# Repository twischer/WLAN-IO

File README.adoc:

WLAN-IO
=======

WLAN-RGB-Para
-------------
The ESP8266 is used as an Art-Net-Node and the 3 output pins will be used as PWM outputs. So a RGB-LED could be directly connected and controlled over WLAN.
The inital version was copied from http://www.ulrichradig.de/home/index.php/dmx/wlan-art-net-node.

### Building WLAN-RGB-Para with MQTT and Art-Net support
    $ make COMPONENTS="io/mqtt io/pwm io/artnet"
See schematics/LEDDriver.sch

### Energy consumtion
Supply	Off				On
4,8V	75mA (360mW)
8V		75mA (600mW)	3,40A (27,2W)
10V						2,58A
12V						2,03A
14V						1,68A
15V		75mA (1,13W)	1,57A (23,6W)

Building for heater controll and DHT22 support controlling over MQTT
--------------------------------------------------------------------
    $ make COMPONENTS="io/mqtt io/heater io/dhtxx"
See schematics/dhtxx+heater.sch for a wiring example.

Building for shift phase dimmer with zero crossing detection
------------------------------------------------------------
This build supports MQTT, too.
It will be build for ESP8266 on the module ESP03.
Default is ESP02.
    $ make COMPONENTS="io/mqtt io/pwm io/pwm/zcd" DEFINES="-DESP03 -DPWM_CHANNEL=1 -DPWM_INVERTED"
See schematics/dimmerWall.sch for the needed components to run.

HOWTO test mosquitto (MQTT broker)
----------------------------------
    $ sudo apt-get install mosquitto mosquitto-clients

    $ mosquitto_pub -h [HOST] -m hello -t test -r

    $ mosquitto_sub -h [HOST] -t test -d

ESP-LINK: Wifi-Serial Bridge w/REST&MQTT
========================================
Thorsten von Eicken
:toc:
:toc-title!:
:toc-placement!:

This firmware connects an attached micro-controller to the internet using a ESP8266 Wifi module.
It implements a number of features:

[options="compact"]
- transparent bridge between Wifi and serial, useful for debugging or inputting into a uC
- flash-programming attached Arduino/AVR microcontrollers, esp8266 modules, as well as
  LPC800-series and other ARM microcontrollers via Wifi
- built-in stk500v1 programmer for AVR uC's: program using HTTP upload of hex file
- outbound REST HTTP requests from the attached micro-controller to the internet
- MQTT client pub/sub from the attached micro-controller to the internet

The firmware includes a tiny HTTP server based on
http://www.esp8266.com/viewforum.php?f=34[esphttpd]
with a simple web interface, many thanks to Jeroen Domburg for making it available!
The REST and MQTT functionality are loosely based on https://github.com/tuanpmt/espduino
but significantly reqritten and no longer protocol compatible, thanks to tuanpmt for the
inspiration!

Many thanks to https://github.com/brunnels for contributions in particular around the espduino
functionality. Thank you also to https://github.com/susisstrolch, https://github.com/bc547,
and https://github.com/katast for additional contributions!

[float]
Table of Contents
-----------------

toc::[]

Releases & Downloads
--------------------

- https://github.com/jeelabs/esp-link/releases/tag/v2.1.7[V2.1.7] is the most recent release.
  It has the new built-in stk500v1 programmer and works on all modules (esp-01 through esp-12).
- https://github.com/jeelabs/esp-link/releases/tag/v2.2.beta2[V2.2.beta2] will be coming
  up shortly with mDNS, sNTP, and syslog support, stay tuned...
- See https://github.com/jeelabs/esp-link/releases[all releases].

For quick support and questions chat at
image:https://badges.gitter.im/Join%20Chat.svg[link="https://gitter.im/jeelabs/esp-link"]

Intro
-----

### Esp-link goals

The goal of the esp-link project is to create an advanced Wifi co-processor. Esp-link assumes that
there is a "main processor" (also referred to as "attached uController") and that esp-link's role
is to facilitate communication over Wifi. Where esp-link is a bit unusual is that it's not really
just a Wifi interface or a slave co-processor. In some sense it's the master, because the main
processor can be reset, controlled and reprogrammed through esp-link. The three main areas of
functionality in esp-link are:

- reprogramming and debugging the attached uC
- letting the attached uC make outbound communication and offloading the protocol processing
- forwarding inbound communication and offloading the protocol processing (this part is the
least developed)

The goal of the project is also to remain focused on the above mission. In particular, esp-link
is not a platform for stand-alone applications and it does not support connecting sensors or
actuators directly to it. A few users have taken esp-link as a starting point for doing these
things and that's great, but there's also value in keeping the mainline esp-link project
focused on a clear mission.

### Esp-link uses

The simplest use of esp-link is as a transparent serial to wifi bridge. You can flash an attached
uC over wifi and you can watch the uC's serial debug output by connecting to port 23 or looking
at the uC Console web page.

The next level is to use the outbound connectivity of esp-link in the uC code. For example, the
uC can use REST requests to services like thingspeak.com to send sensor values that then get
stored and plotted by the external service.
The uC can also use REST requests to retrieve simple configuration
information or push other forms of notifications. (MQTT functionality is forthcoming.)

An additional option is to add code to esp-link to customize it and put all the communication
code into esp-link and only keep simple sensor/actuator control in the attached uC. In this
mode the attached uC sends custom commands to esp-link with sensor/acturator info and
registers a set of callbacks with esp-link that control sensors/actuators. This way, custom
commands in esp-link can receive MQTT messages, make simple callbacks into the uC to get sensor
values or change actuators, and then respond back with MQTT. The way this is architected is that
the attached uC registers callbacks at start-up such that the code in the esp doesn't need to 
know which exact sensors/actuators the attached uC has, it learns that through the initial
callback registration.

### Eye Candy

These screen shots show the Home page, the Wifi configuration page, the console for the
attached microcontroller, and the pin assignments card:

image:https://cloud.githubusercontent.com/assets/39480/8261425/6ca395a6-167f-11e5-8e92-77150371135a.png[width="45%"]
image:https://cloud.githubusercontent.com/assets/39480/8261427/6caf7326-167f-11e5-8085-bc8b20159b2b.png[width="45%"]
image:https://cloud.githubusercontent.com/assets/39480/8261426/6ca7f75e-167f-11e5-827d-9a1c582ad05d.png[width="45%"]
image:https://cloud.githubusercontent.com/assets/39480/8261658/11e6c64a-1681-11e5-82d0-ea5ec90a6ddb.png[width="45%"]

Getting Started
---------------

### Hardware configuration

This firmware is designed for any esp8266 module.
The recommended connections for an esp-01 module are:

- URXD: connect to TX of microcontroller
- UTXD: connect to RX of microcontroller
- GPIO0: connect to RESET of microcontroller
- GPIO2: optionally connect green LED to 3.3V (indicates wifi status)

The recommended connections for an esp-12 module are:

- URXD: connect to TX of microcontroller
- UTXD: connect to RX of microcontroller
- GPIO12: connect to RESET of microcontroller
- GPIO13: connect to ISP of LPC/ARM microcontroller or to GPIO0 of esp8266 being programmed
  (not used with Arduino/AVR)
- GPIO0: optionally connect green "conn" LED to 3.3V (indicates wifi status)
- GPIO2: optionally connect yellow "ser" LED to 3.3V (indicates serial activity)

If your application has problems with the boot message that is output at ~74600 baud by the ROM
at boot time you can connect an esp-12 module as follows and choose the "swap_uart" pin assignment
in the esp-link web interface:

- GPIO13: connect to TX of microcontroller
- GPIO15: connect to RX of microcontroller
- GPIO1/UTXD: connect to RESET of microcontroller
- GPIO3/URXD: connect to ISP of LPC/ARM microcontroller or to GPIO0 of esp8266 being programmed
  (not used with Arduino/AVR)
- GPIO0: optionally connect green "conn" LED to 3.3V (indicates wifi status)
- GPIO2: optionally connect yellow "ser" LED to 3.3V (indicates serial activity)

If you are using an FTDI connector, GPIO12 goes to DTR and GPIO13 goes to CTS (or vice-versa, I've
seen both used, sigh).

The GPIO pin assignments can be changed dynamically in the web UI and are saved in flash.

### Initial flashing

If you want to simply flash a pre-built firmware binary, you can download the latest
https://github.com/jeelabs/esp-link/releases[release] and use your favorite
ESP8266 flashing tool to flash the bootloader, the firmware, and blank settings.
Detailed instructions are provided in the release notes.

_Important_: the firmware adapts automatically to the size of the flash chip using information
stored in the boot sector (address 0). This is the standard way that the esp8266 SDK detects
the flash size. What this means is that you need to set this properly when you flash the bootloader.
If you use esptool.py you can do it using the -ff and -fs options.

### Wifi configuration overview

For proper operation the end state that esp-link needs to arrive at is to have it
join your pre-existing wifi network as a pure station.
However, in order to get there esp-link will start out as an access point and you'll have
to join its network to configure it. The short version is:

 1. esp-link creates a wifi access point with an SSID of the form `ESP_012ABC` (some modules
    use a different SSID form, such as `ai-thinker-012ABC`)
 2. you join your laptop or phone to esp-link's network as a station and you configure
    esp-link wifi with your network info by pointing your browser at `http://192.168.4.1/`
 3. you set a hostname for esp-link on the "home" page, or leave the default ("esp-link")
 4. esp-link starts to connect to your network while continuing to also be an access point
    ("AP+STA"), the esp-link may show up with a `${hostname}.local` hostname
    (depends on your DHCP/DNS config)
 4. esp-link succeeds in connecting and shuts down its own access point after 15 seconds,
    you reconnect your laptop/phone to your normal network and access esp-link via its hostname
    or IP address

### LED indicators

Assuming appropriate hardware attached to GPIO pins, the green "conn" LED will show the wifi
status as follows:

- Very short flash once a second: not connected to a network and running as AP+STA, i.e.
  trying to connect to the configured network
- Very short flash once every two seconds: not connected to a network and running as AP-only
- Even on/off at 1HZ: connected to the configured network but no IP address (waiting on DHCP)
- Steady on with very short off every 3 seconds: connected to the configured network with an
  IP address (esp-link shuts down its AP after 60 seconds)

The yellow "ser" LED will blink briefly every time serial data is sent or received by the esp-link.

### Troubleshooting

- verify that you have sufficient power, borderline power can cause the esp module to seemingly
  function until it tries to transmit and the power rail collapses
- if you just cannot flash your esp8266 module (some people call it the zombie mode) make sure you
  have gpio0 and gpio15 pulled to gnd with a 1K resistor, gpio2 tied to 3.3V with 1K resistor, and
  RX/TX connected without anything in series. If you need to level shift the signal going into the
  esp8266's RX use a 1K resistor. Use 115200 baud in the flasher.
  (For a permanent set-up I would use higher resistor values but
  when nothing seems to work these are the ones I try.)
- if the flashing succeeded, check the "conn" LED to see which mode esp-link is in (see LED info above)
- reset or power-cycle the esp-link to force it to become an access-point if it can't
  connect to your network within 15-20 seconds
- if the LED says that esp-link is on your network but you can't get to it, make sure your
  laptop is on the same network (and no longer on the esp's network)
- if you do not know the esp-link's IP address on your network, try `esp-link.local`, try to find
  the lease in your DHCP server; if all fails, you may have to turn off your access point (or walk
  far enough away) and reset/power-cycle esp-link, it will then fail to connect and start its
  own AP after 15-20 seconds

Configuration details
---------------------

### Wifi

After you have serially flashed the module it will create a wifi access point (AP) with an
SSID of the form `ESP_012ABC` where 012ABC is a piece of the module's MAC address.
Using a laptop, phone, or tablet connect to this SSID and then open a browser pointed at
http://192.168.4.1/, you should then see the esp-link web site.

Now configure the wifi. The desired configuration is for the esp-link to be a
station on your local wifi network so you can communicate with it from all your computers.

To make this happen, navigate to the wifi page and you should see the esp-link scan
for available networks. You should then see a list of detected networks on the web page and you
can select yours.
Enter a password if your network is secure (highly recommended...) and hit the connect button.

You should now see that the esp-link has connected to your network and it should show you
its IP address. _Write it down_. You will then have to switch your laptop, phone, or tablet
back to your network and then you can connect to the esp-link's IP address or, depending on your
network's DHCP/DNS config you may be able to go to http://esp-link.local

At this point the esp-link will have switched to STA mode and be just a station on your
wifi network. These settings are stored in flash and thereby remembered through resets and
power cycles. They are also remembered when you flash new firmware. Only flashing `blank.bin`
via the serial port as indicated above will reset the wifi settings.

There is a fail-safe, which is that after a reset or a configuration change, if the esp-link
cannot connect to your network it will revert back to AP+STA mode after 15 seconds and thus
both present its `ESP_012ABC`-style network and continue trying to reconnect to the requested network.
You can then connect to the esp-link's AP and reconfigure the station part.

One open issue (#28) is that esp-link cannot always display the IP address it is getting to the browser
used to configure the ssid/password info. The problem is that the initial STA+AP mode may use
channel 1 and you configure it to connect to an AP on channel 6. This requires the ESP8266's AP
to also switch to channel 6 disconnecting you in the meantime. 

### Hostname, description, DHCP, mDNS

You can set a hostname on the "home" page, this should be just the hostname and not a domain
name, i.e., something like "test-module-1" and not "test-module-1.mydomain.com".
This has a number of effects:

- you will see the first 12 chars of the hostname in the menu bar (top left of the page) so
  if you have multiple modules you can distinguish them visually
- esp-link will use the hostname in its DHCP request, which allows you to identify the module's
  MAC and IP addresses in your DHCP server (typ. your wifi router). In addition, some DHCP
  servers will inject these names into the local DNS cache so you can use URLs like
  `hostname.local`.
- someday, esp-link will inject the hostname into mDNS (multicast DNS, bonjour, etc...) so 
  URLs of the form `hostname.local` work for everyone (as of v2.1.beta5 mDNS is disabled due
  to reliability issues with it)

You can also enter a description of up to 128 characters on the home page (bottom right). This
allows you to leave a memo for yourself, such as "installed in basement to control the heating
system". This descritpion is not used anywhere else.

Building the firmware
---------------------

### Linux

The firmware has been built using the https://github.com/pfalcon/esp-open-sdk[esp-open-sdk]
on a Linux system. Create an esp8266 directory, install the esp-open-sdk into a sub-directory
using the *non-standalone* install (i.e., there should not be an sdk directory in the esp-open-sdk
dir when done installing, if you use the standalone install you will get compilation errors
with std types, such as `uint32_t`).

Download the Espressif SDK (use the version mentioned in the release notes) from their
http://bbs.espressif.com/viewforum.php?f=5[download forum] and also expand it into a
sub-directory.

Clone the esp-link repository into a third sub-directory and check out the tag you would like,
such as `git checkout v2.1.7`.
This way the relative paths in the Makefile will work.
If you choose a different directory structure look at the Makefile for the appropriate environment
variables to define.
Do not use the source tarballs from the release page on github,
these will give you trouble compiling because the Makefile uses git to determine the esp-link
version being built.

In order to OTA-update the esp8266 you should `export ESP_HOSTNAME=...` with the hostname or
IP address of your module.

Now, build the code: `make` in the top-level of esp-link. If you want to se the commands being
issued, use `VERBOSE=1 make`.

A few notes from others (I can't fully verify these):

- You may need to install `zlib1g-dev` and `python-serial`
- Make sure you have the correct version of the esp_iot_sdk
- Make sure the paths at the beginning of the makefile are correct
- Make sure `esp-open-sdk/xtensa-lx106-elf/bin` is in the PATH set in the Makefile

### Windows

It is possible to build esp-link on Windows, but it requires a gaggle of software to be installed:

- Install the unofficial sdk, mingw, SourceTree (gui git client), python 2.7, git cli, Java
- Use SourceTree to checkout under C:\espressif or wherever you installed the unofficial sdk,
  (see this thread for the unofficial sdk http://www.esp8266.com/viewtopic.php?t=820)
- Create a symbolic link under c:/espressif for the git bin directory under program files and
  the java bin directory under program files.
- ...

### Updating the firmware over-the-air

This firmware supports over-the-air (OTA) flashing, so you do not have to deal with serial
flashing again after the initial one! The recommended way to flash is to use `make wiflash`
if you are also building the firmware.
If you are downloading firmware binaries use `./wiflash`.
`make wiflash` assumes that you set `ESP_HOSTNAME` to the hostname or IP address of your esp-link.
You can easily do that using something like `ESP_HOSTNAME=192.168.1.5 make wiflash`.

The flashing, restart, and re-associating with your wireless network takes about 15 seconds
and is fully automatic. The first 1MB of flash are divided into two 512KB partitions allowing for new
code to be uploaded into one partition while running from the other. This is the official
OTA upgrade method supported by the SDK, except that the firmware is POSTed to the module
using curl as opposed to having the module download it from a cloud server. On a module with
512KB flash there is only space for one partition and thus no way to do an OTA update.

If you are downloading the binary versions of the firmware (links forthcoming) you need to have
both `user1.bin` and `user2.bin` handy and run `wiflash.sh <esp-hostname> user1.bin user2.bin`.
This will query the esp-link for which file it needs, upload the file, and then reconnect to
ensure all is well.

Note that when you flash the firmware the wifi settings are all preserved so the esp-link should
reconnect to your network within a few seconds and the whole flashing process should take 15-30
from beginning to end. If you need to clear the wifi settings you need to reflash the `blank.bin`
using the serial port.

The flash configuration and the OTA upgrade process is described in more detail in [FLASH.md](FLASH.md)

Serial bridge and connections to Arduino, AVR, ARM, LPC microcontrollers
------------------------------------------------------------------------

In order to connect through the esp-link to a microcontroller use port 23. For example,
on linux you can use `nc esp-hostname 23` or `telnet esp-hostname 23`.

Note that multiple connections to port 23 and 2323 can be made simultaneously. Esp-link will
intermix characters received on all these connections onto the serial TX and it will
broadcast incoming characters from the serial RX to all connections. Use with caution!

### Flashing an attached AVR/Arduino

There are three options for reprogramming an attached AVR/Arduino microcontroller:

- Use avrdude and point it at port 23 of esp-link. Esp-link automatically detects the programming
  sequence and issues a reset to the AVR.
- Use avrdude and point it at port 2323 of esp-link. This is the same as port 23 except that the
  autodectection is not used and the reset happens because port 2323 is used
- Use curl or a similar tool to HTTP POST the firmware to esp-link. This uses the built-in
  programmer, which only works for AVRs/Arduinos with the optiboot bootloader (which is std).

To reprogram an Arduino / AVR microcontroller by pointing avrdude at port 23 or 2323 you
specify a serial port of the form `net:esp-link:23` in avrdude's -P option, where
`esp-link` is either the hostname of your esp-link or its IP address).
This is instead of specifying a serial port of the form /dev/ttyUSB0.
Esp-link detects that avrdude starts its connection with a flash synchronization sequence
and sends a reset to the AVR microcontroller so it can switch into flash programming mode.

To reprogram using the HTTP POST method you need to first issue a POST to put optiboot into
programming mode: POST to `http://esp-link/pgm/sync`, this starts the process. Then check that
synchronization with optiboot has been achieved by issuing a GET to the same URL
(`http://esp-link/pgm/sync`). Repeat until you have sync (takes <500ms normally). Finally
issue a POST request to `http://esp-link/pgm/upload` with your hex file as POST data (raw,
not url-encoded or multipart-mime. Please look into the avrflash script for the curl command-line
details or use that script directly (`./avrflash esp-link.local my_sketch.hex`).
_Important_: after the initial sync request that resets the AVR you have 10 seconds to get to the
upload post or esp-link will time-out. So if you're manually entering curl commands have them
prepared so you can copy&paste!

Beware of the baud rate, which you can set on the uC Console page. Sometimes you may be using
115200 baud in sketches but the bootloader may use 57600 baud. When you use port 23 or 2323 you
need to set the baud rate correctly. If you use the built-in programmer (HTTP POST method) then
esp-link will try the configured baud rate and also 9600, 57600, and 115200 baud, so it should
work even if you have the wrong baud rate configured...

When to use which method? If port 23 works then go with that. If you have trouble getting sync
or it craps out in the middle too often then try the built-in programmer with the HTTP POST.
If your AVR doesn't use optiboot then use port 2323 since esp-link may not recognize the programming
sequence and not issue a reset if you use port 23.

If you are having trouble with the built-in programmer and see something like this:

--------------------
# ./avrflash 192.168.3.104 blink.hex
Error checking sync: FAILED to SYNC: abandoned after timeout, got:
:\xF/\x00\xCj\xCz\xCJ\xCZ\xC\xAÜ\xC\xAä\xC\xAÜ\xC\xAä\xC\xBì\xC\xBô\xC\xBì\xC\xBô\xC\xAÜ\xC\xAä\xC
--------------------

the most likely cause is a baud rate mismatch and/or a bad connection from the esp8266 to the
AVRs reset line.
The baud rate used by esp-link is set on the uC Console web page and, as mentioned above, it will
automatically try 9600, 57600, and 115200 as well.
The above garbage characters are most likely due to optiboot timing out and starting the sketch
and then the sketch sending data at a different baud rate than configured into esp-link.
Note that sketches don't necessarily use the same baud rate as optiboot, so you may have the
correct baud rate configured but reset isn't functioning, or reset may be functioning but the
baud rate may be incorrect.

The output of a successful flash using the built-in programmer looks like this:

--------------------
Success. 3098 bytes at 57600 baud in 0.8s, 3674B/s 63% efficient
--------------------

This says that the sketch comprises 3098 bytes of flash, was written in 0.8 seconds
(excludes the initial sync time) at 57600 baud,
and the 3098 bytes were flashed at a rate of 3674 bytes per second.
The efficiency measure is the ratio of the actual rate to the serial baud rate,
thus 3674/5760 = 0.63 (there are 10 baud per character).
The efficiency is not 100% because there is protocol overhead (such as sync, record type, and
length characters)
and there is dead time waiting for an ack or preparing the next record to be sent.

### Details of built-in AVR flash algorithm

The built-in flashing algorithm differs a bit from what avrdude does. The programming protocol
states that STK_GET_SYNC+CRC_EOP (0x30 0x20) should be sent to synchronize, but that works poorly
because the AVR's UART only buffers one character. This means that if STK_GET_SYNC+CRC_EOP is
sent twice there is a high chance that only the last character (CRC_EOP) is actually
received. If that is followed by another STK_GET_SYNC+CRC_EOP sequence then optiboot receives
CRC_EOP+STK_GET_SYNC+CRC_EOP which causes it to abort and run the old sketch. Ending up in that
situation is quite likely because optiboot initializes the UART as one of the first things, but
then goes off an flashes an LED for ~300ms during which it doesn't empty the UART.

Looking at the optiboot code, the good news is that CRC_EOP+CRC_EOP can be used to get an initial
response without the overrun danger of the normal sync sequence and this is what esp-link does.
The programming sequence runs as follows:

- esp-link sends a brief reset pulse (1ms)
- esp-link sends CRC_EOP+CRC_EOP ~50ms later
- esp-link sends CRC_EOP+CRC_EOP every ~70-80ms
- eventually optiboot responds with STK_INSYNC+STK_OK (0x14;0x10)
- esp-link sends one CRC_EOP to sort out the even/odd issue
- either optiboot responds with STK_INSYNC+STK_OK or nothing happens for 70-80ms, in which case
  esp-link sends another CRC_EOP
- esp-link sends STK_GET_SYNC+CRC_EOP and optiboot responds with STK_INSYNC+STK_OK and we're in
  sync now
- esp-link sends the next command (starts with 'u') and programming starts...

If no sync is achieved, esp-link changes baud rate and the whole thing starts over with a reset
pulse about 600ms, esp-link gives up after about 5 seconds and reports an error.

### Flashing an attached ARM processor

You can reprogram NXP's LPC800-series and many other ARM processors as well by pointing your
programmer similarly at the esp-link's port 23. For example, if you are using
https://github.com/jeelabs/embello/tree/master/tools/uploader a command line like
`uploader -t -s -w esp-link:23 build/firmware.bin` does the trick.
The way it works is that the uploader uses telnet protocol escape sequences in order to
make esp-link issue the appropriate "ISP" and reset sequence to the microcontroller to start the
flash programming. If you use a different ARM programming tool it will work as well as long as
it starts the connection with the `?\r\n` synchronization sequence.

### Flashing an attached esp8266

Yes, you can use esp-link running on one esp8266 module to flash another esp8266 module,
however it is rather tricky! The problem is not electric, it is wifi interference.
The basic idea is to use some method to direct the esp8266 flash program to port 2323 of
esp-link. Using port 2323 with the appropriate wiring will cause the esp8266's reset and 
gpio0 pins to be toggled such that the chip enters the flash programming mode.

One option for connecting the programmer with esp-link is to use my version of esptool.py
at http://github.com/tve/esptool, which supports specifying a URL instead of a port. Thus
instead of specifying something like `--port /dev/ttyUSB0` or `--port COM1` you specify
`--port socket://esp-link.local:2323`. Important: the baud rate specified on the esptool.py
command-line is irrelevant as the baud rate used by esp-link will be the one set in the
uC console page. Fortunately the esp8266 bootloader does auto-baud detection. (Setting the
baud rate to 115200 is recommended.)

Another option is to use a serial-to-tcp port forwarding driver and point that to port 2323
of esp-link. On windows users have reported success with
http://www.hw-group.com/products/hw_vsp/hw_vsp2_en.html[HW Virtual Serial Port]

Now to the interference problem: once the attached esp8266 is reset it
starts outputting its 26Mhz clock on gpio0, which needs to be attached to
the esp8266 running esp-link (since it needs to drive gpio0 low during
the reset to enter flash mode). This 26Mhz signal on gpio0 causes a
significant amount of radio interference with the result that the esp8266
running esp-link has trouble receiving Wifi packets. You can observe this
by running a ping to esp-link in another window: as soon as the target
esp8266 is reset, the pings become very slow or stop altogetehr. As soon
as you remove power to the attached esp8266 the pings resume beautifully.

To try and get the interference under control, try some of the following:
add a series 100ohm resistor and 100pf capacitor to ground as close to
the gpio0 pin as possible (basically a low pass filter); and/or pass
the cable connecting the two esp8266's through a ferrite bead.

### Debug log

The esp-link web UI can display the esp-link debug log (os_printf statements in the code). This
is handy but sometimes not sufficient. Esp-link also prints the debug info to the UART where
it is sometimes more convenient and sometimes less... For this reason three UART debug log
modes are supported that can be set in the web UI (and the mode is saved in flash):

- auto: the UART log starts enabled at boot using uart0 and disables itself when esp-link
  associates with an AP. It re-enables itself if the association is lost.
- off: the UART log is always off
- on0: the UART log is always on using uart0
- on1: the UART log is always on using uart1 (gpio2 pin)

Note that even if the UART log is always off the ROM prints to uart0 whenever the
esp8266 comes out of reset. This cannot be disabled.

Outbound HTTP REST requests and MQTT client
-------------------------------------------

The V2 versions of esp-link use the SLIP protocol over the serial link to support simple outbound
HTTP REST requests as well as an MQTT client. The SLIP protocol consists of commands with
binary arguments sent from the
attached microcontroller to the esp8266, which then performs the command and responds back.
The responses back use a callback address in the attached microcontroller code, i.e., the
command sent by the uC contains a callback address and the response from the esp8266 starts
with that callback address. This enables asynchronous communication where esp-link can notify the
uC when requests complete or when other actions happen, such as wifi connectivity status changes.

You can find REST and MQTT libraries as well as demo sketches in the
https://github.com/jeelabs/el-client[el-client] repository.

Contact
-------

If you find problems with esp-link, please create a github issue. If you have a question, please
use the gitter chat link at the top of this page.

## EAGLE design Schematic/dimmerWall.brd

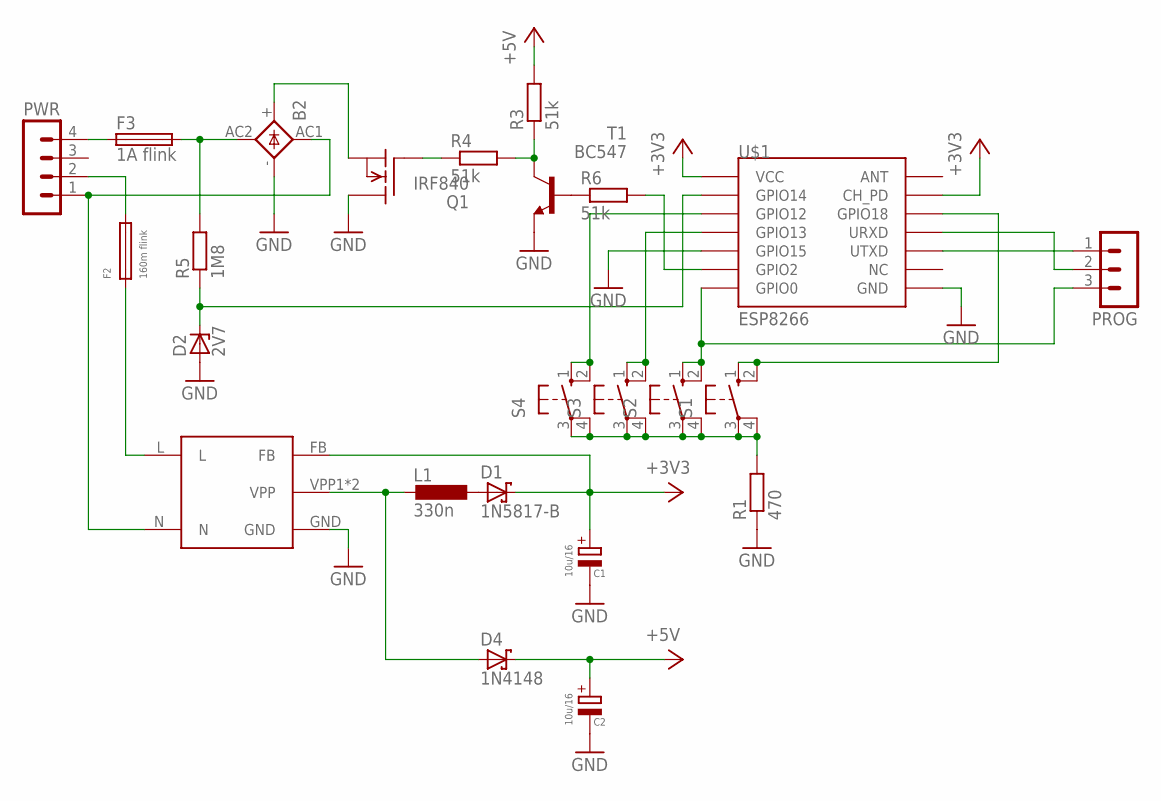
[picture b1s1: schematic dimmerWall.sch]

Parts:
B2: 2KBP
C1, C2: 10u/16; TT2D4L
D1: 1N5817-B; DO41-7.6
D2: 2V7; DO34Z7
D4: 1N4148; DO41-7.6
F2: 160m flink; 19560
F3: 1A flink; SHK20L
L1: 330n; 0204/5
PROG: MA03-1
PWR: MA04-1
Q1: IRF840; TO220
R1: 470; 0207/10
R3: 51k; 0207/12
R4: 51k; 0204/7
R5: 1M8; 0207/12
R6: 51k; 0207/10
S1, S2, S3, S4: 10-XX; B3F-10XX
T1: BC547; TO92
U$1: ESP8266; ESP-03
U$2: SMPS

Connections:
+3V3: C1.+, D1.C, U$1.CH_PD, U$1.VCC, U$2.FB
+5V: C2.+, D4.C, R3.2
GND: B2.-, C1.-, C2.-, D2.A, Q1.2 (D), R1.1, T1.1 (E), U$1.GND, U$1.GPIO15, U$2.GND
unnamed: Q1.1 (G), R4.1
unnamed: R3.1, R4.2, T1.3 (C)
unnamed: D1.A, L1.1
unnamed: B2.AC1, PWR.1, U$2.N
unnamed: R6.1, T1.2 (B)
unnamed: D4.A, L1.2, U$2.VPP1 (VPP), U$2.VPP2 (VPP)
unnamed: D2.C, R5.1, U$1.GPIO14
unnamed: F2.2, PWR.2
unnamed: F2.1, U$2.L
unnamed: R6.2, U$1.GPIO2
unnamed: PROG.1, U$1.UTXD
unnamed: PROG.2, U$1.URXD
unnamed: PROG.3, S2.1 (S), S2.2 (S1), U$1.GPIO0
unnamed: S3.1 (S), S3.2 (S1), U$1.GPIO13
unnamed: S1.1 (S), S1.2 (S1), U$1.GPIO18
unnamed: S4.1 (S), S4.2 (S1), U$1.GPIO12
unnamed: B2.AC2, F3.2A (2), R5.2
unnamed: R1.2, S1.3, S1.4 (P1), S2.3, S2.4 (P1), S3.3, S3.4 (P1), S4.3, S4.4 (P1)
unnamed: B2.+, Q1.3 (S)
unnamed: F3.1A (1), PWR.4

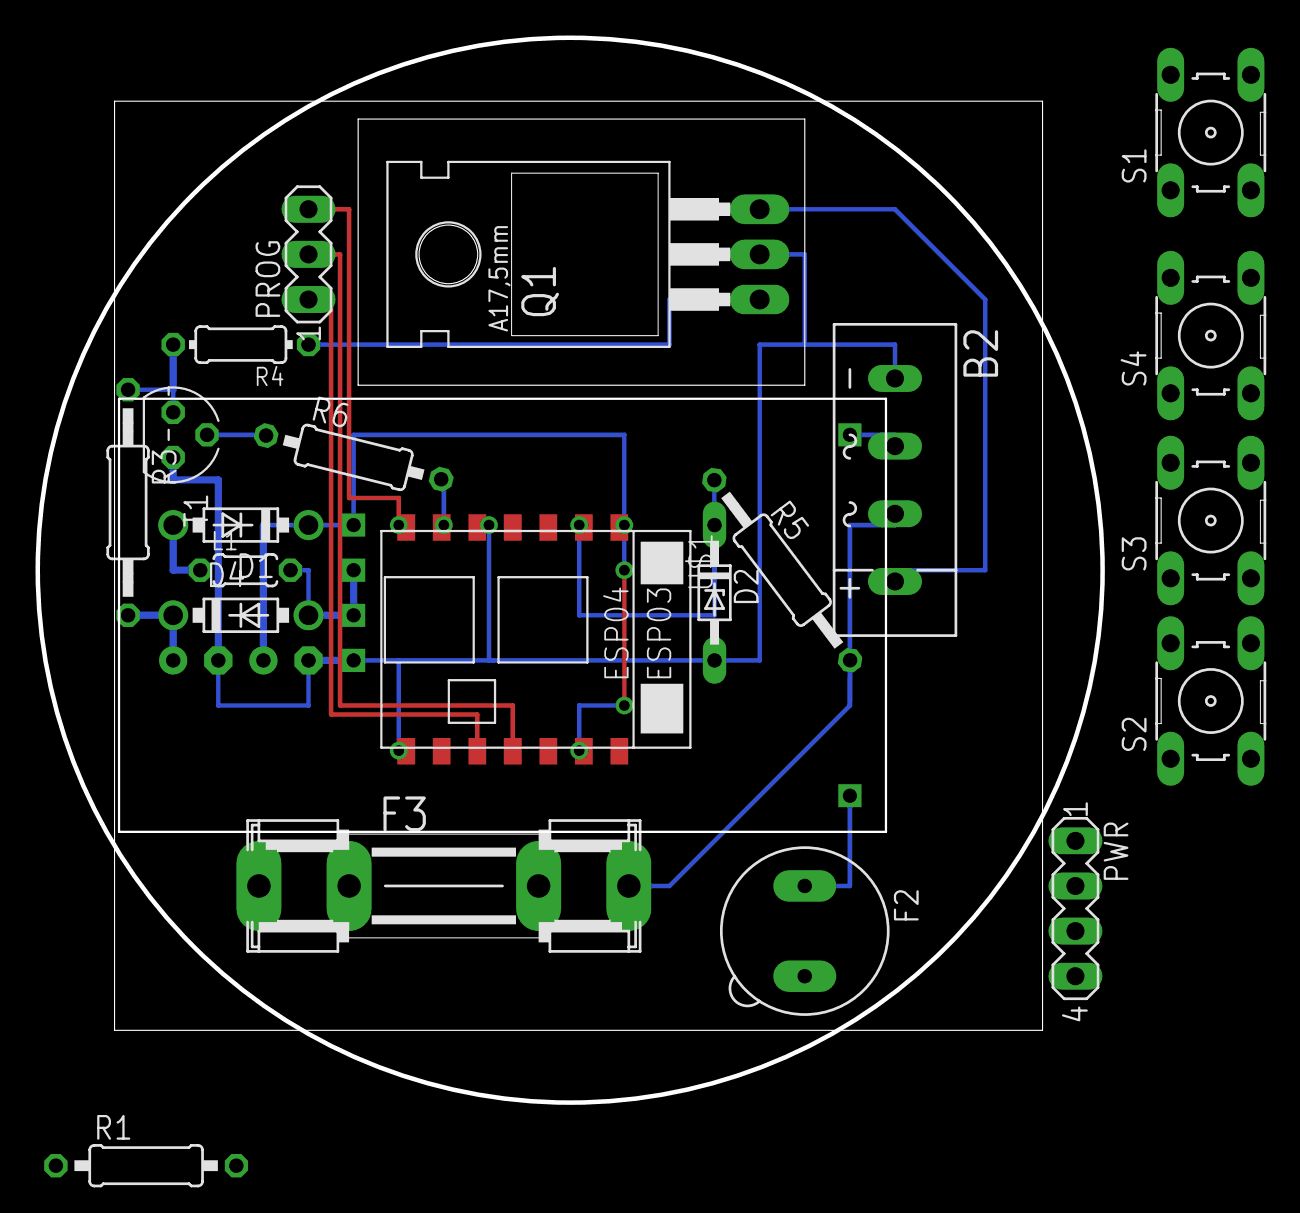
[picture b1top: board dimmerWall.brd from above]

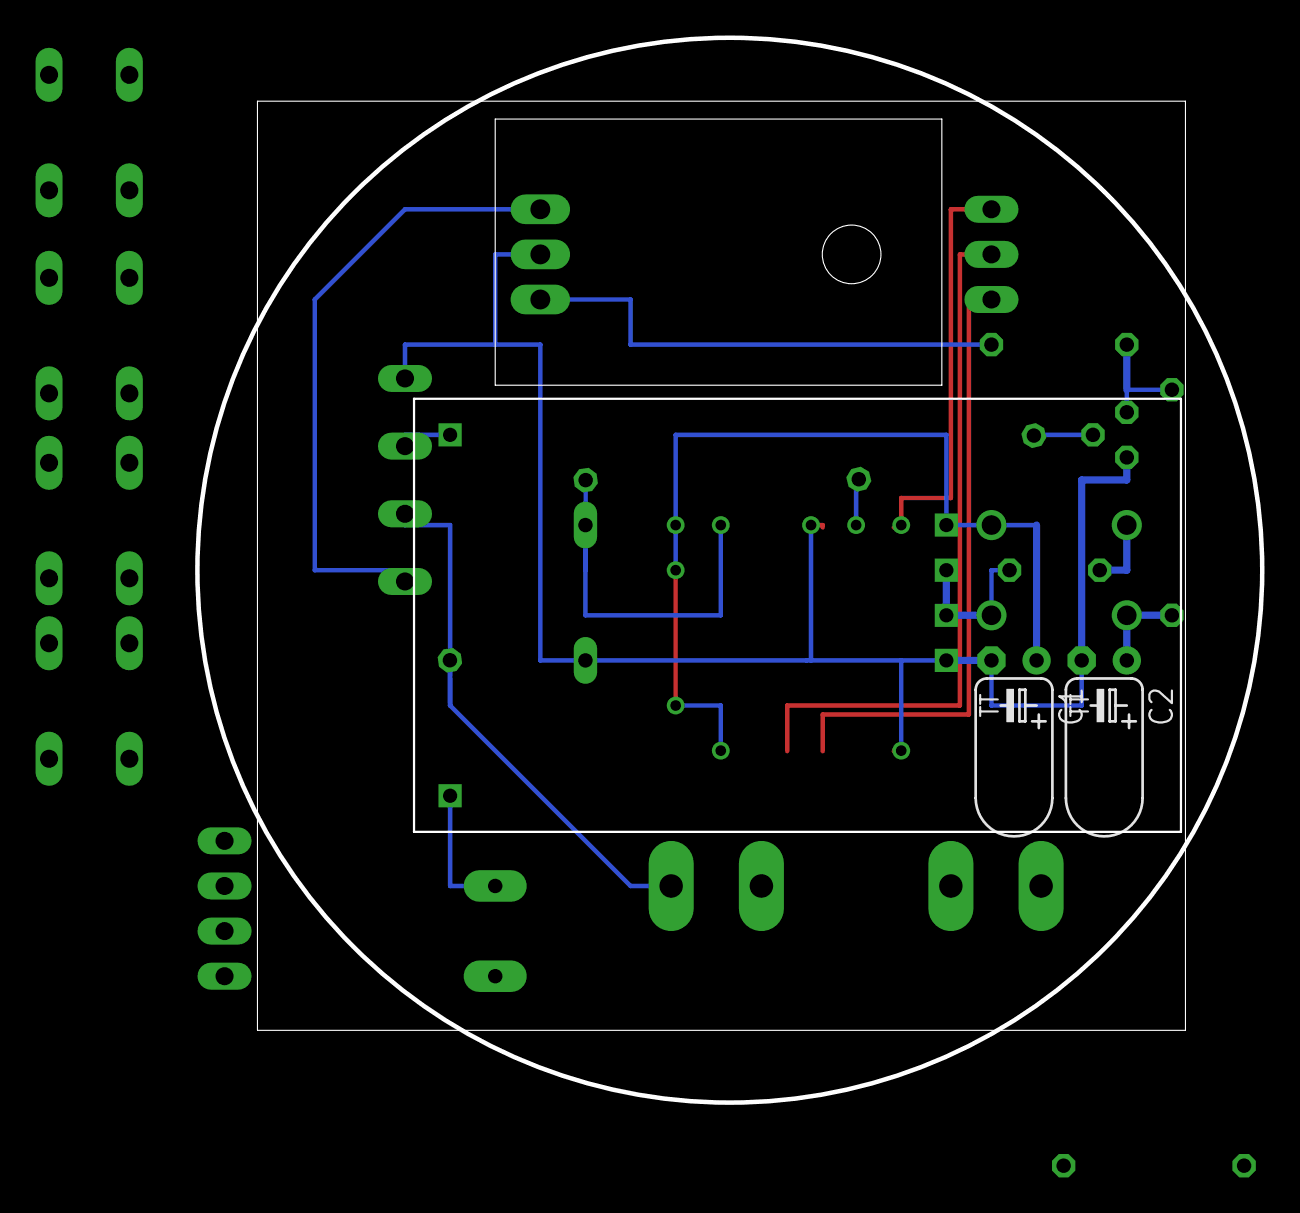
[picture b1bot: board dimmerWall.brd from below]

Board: 2 copper layers, 60.0 x 60.0 mm, 24 parts (2 on the bottom side), 23 nets.

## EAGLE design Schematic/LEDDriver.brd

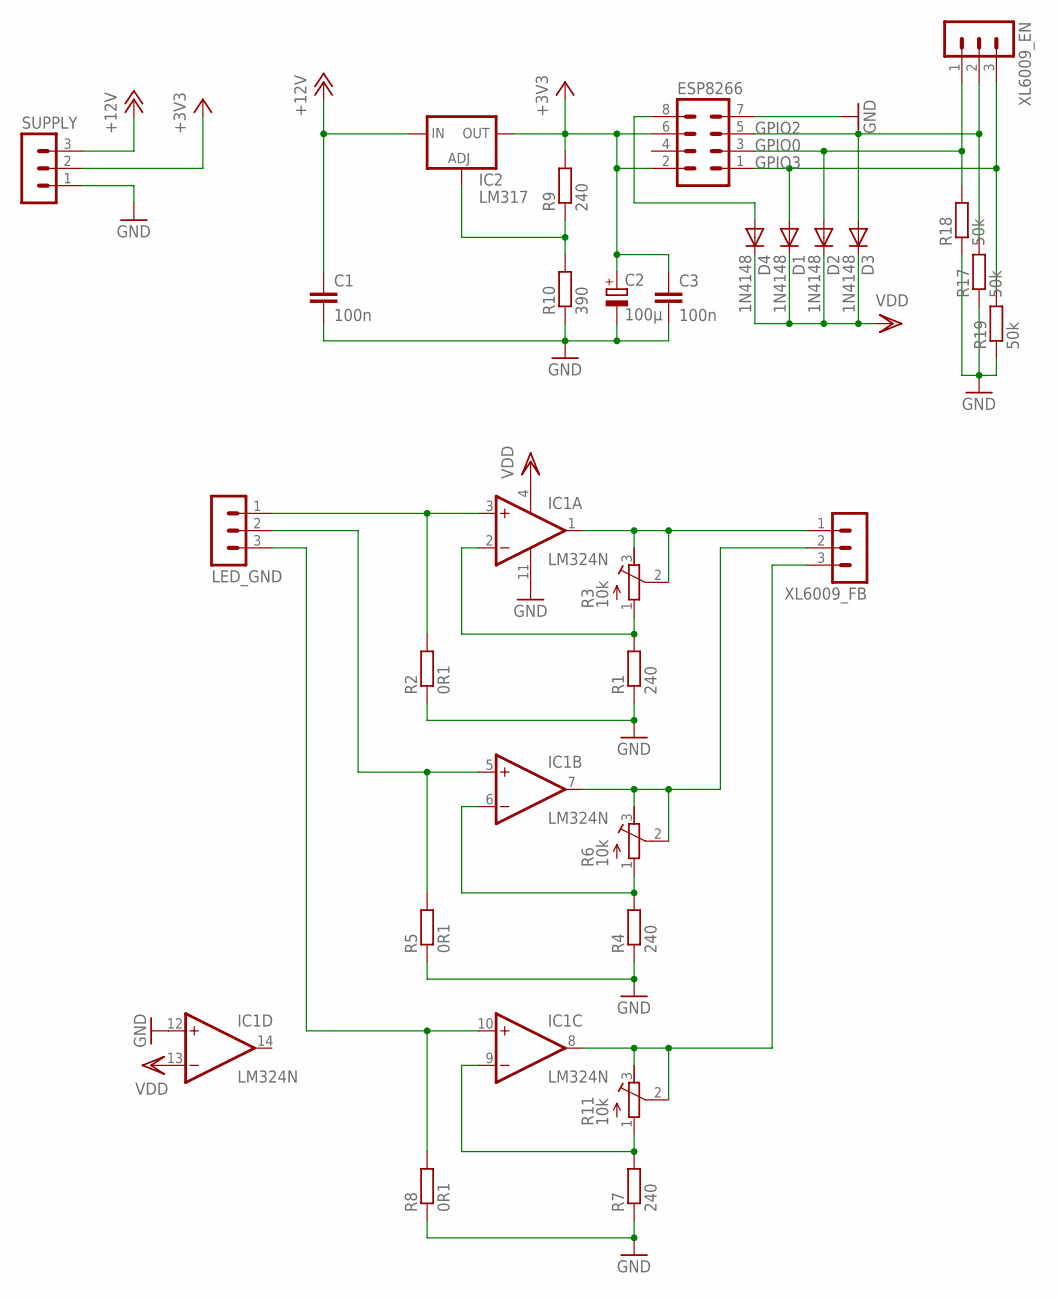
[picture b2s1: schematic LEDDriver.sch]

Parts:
C1, C3: 100n; C075-032X103
C2: 100µ; E5-8,5
D1, D2, D3, D4: 1N4148; D-2.5
ESP8266: MA04-2
IC1: LM324N; DIL14
IC2: LM317; 317TS
LED_GND: MA03-1
R1, R4, R7, R9: 240; 0204V
R2, R5, R8: 0R1; 0204V
R3, R6, R11: 10k; RTRIM64W
R10: 390; 0207/12
R17, R18, R19: 50k; 0207/12
SUPPLY: MA03-1
XL6009_EN, XL6009_FB: MA03-1

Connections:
+3V3: C2.+, C3.1, ESP8266.2, ESP8266.6, IC2.2 (OUT), R9.2, SUPPLY.2
+12V: C1.1, IC2.3 (IN), SUPPLY.3
GND: C1.2, C2.-, C3.2, ESP8266.7, IC1.11 (V-), IC1.12 (+IN), R1.1, R2.1, R4.1, R5.1, R7.1, R8.1, R10.1, R17.1, R18.1, R19.1, SUPPLY.1
GPIO0: D2.A, ESP8266.3, R18.2, XL6009_EN.1
GPIO2: D3.A, ESP8266.5, R17.2, XL6009_EN.2
GPIO3: D1.A, ESP8266.1, R19.2, XL6009_EN.3
unnamed: IC1.2 (-IN), R1.2, R3.1 (A)
unnamed: IC1.3 (+IN), LED_GND.1, R2.2
unnamed: IC1.1 (OUT), R3.2 (S), R3.3 (E), XL6009_FB.1
unnamed: IC2.1 (ADJ), R9.1, R10.2
unnamed: IC1.5 (+IN), LED_GND.2, R5.2
unnamed: IC1.7 (OUT), R6.2 (S), R6.3 (E), XL6009_FB.2
unnamed: IC1.6 (-IN), R4.2, R6.1 (A)
unnamed: IC1.10 (+IN), LED_GND.3, R8.2
unnamed: IC1.8 (OUT), R11.2 (S), R11.3 (E), XL6009_FB.3
unnamed: IC1.9 (-IN), R7.2, R11.1 (A)
unnamed: D4.A, ESP8266.8
VDD: D1.C, D2.C, D3.C, D4.C, IC1.4 (V+), IC1.13 (-IN)

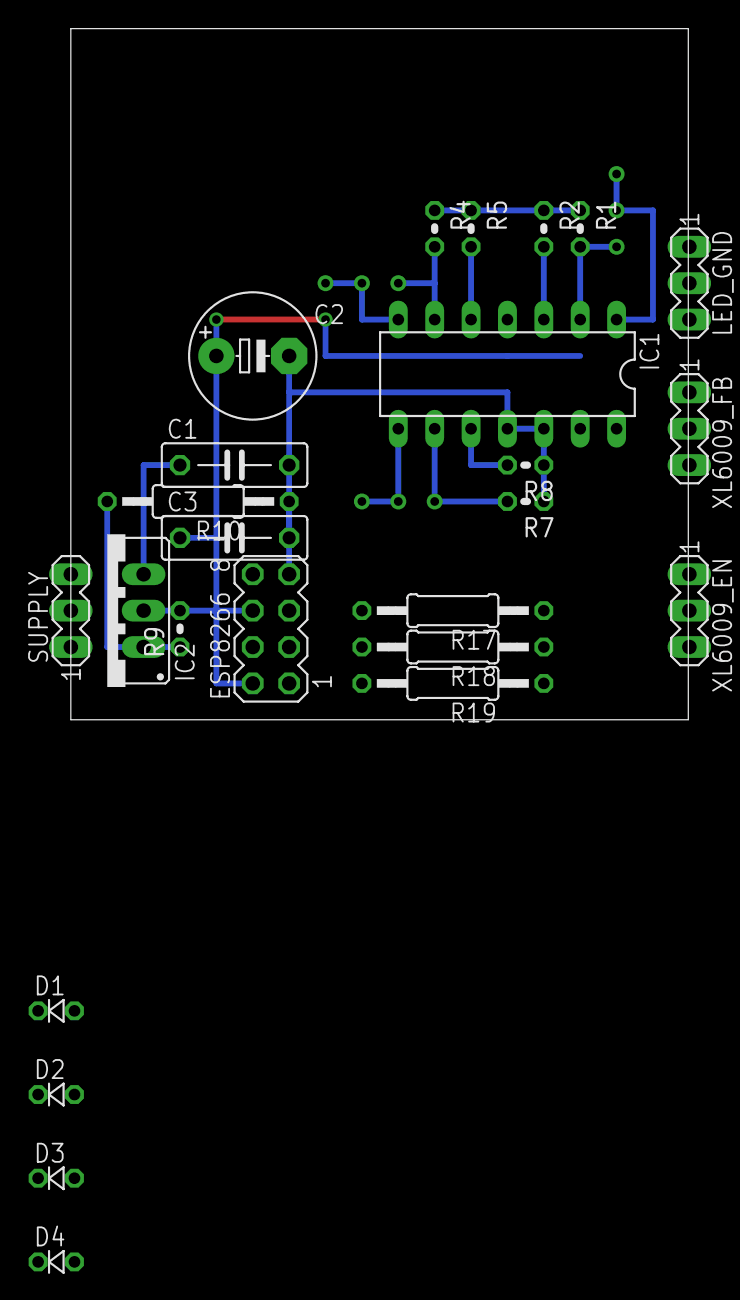
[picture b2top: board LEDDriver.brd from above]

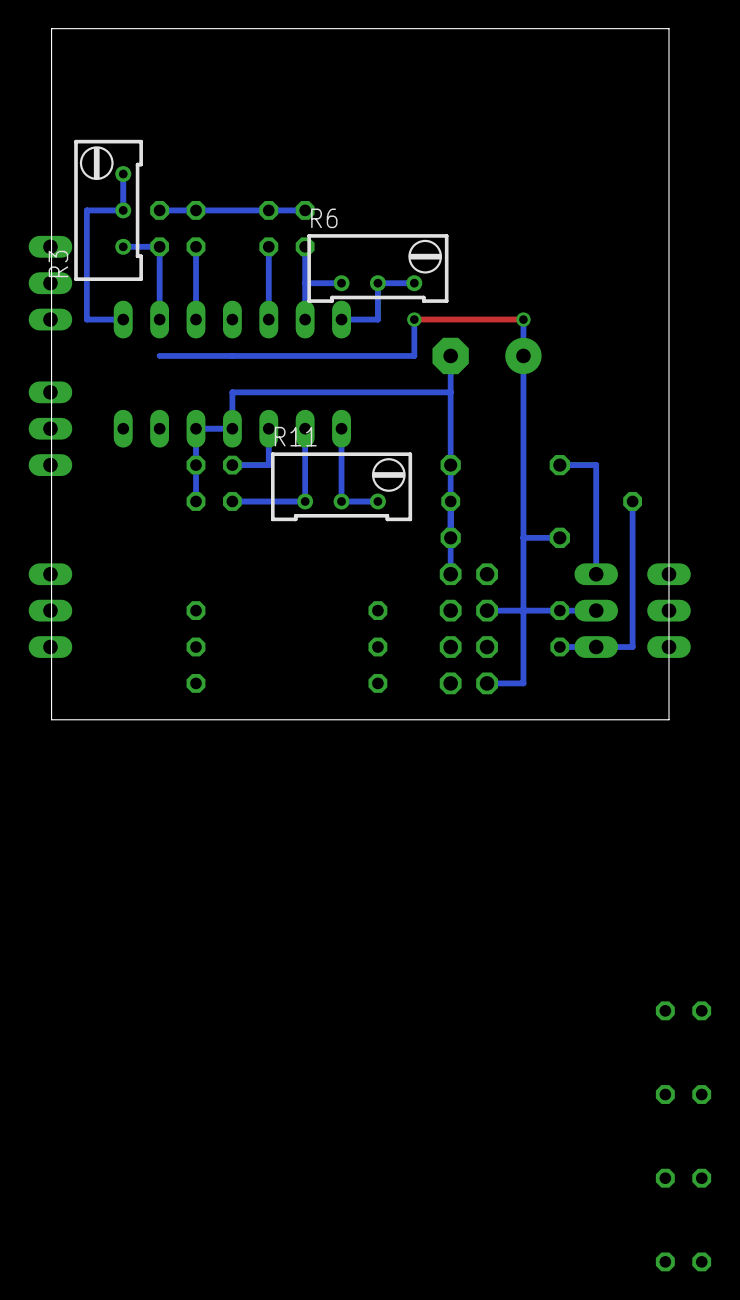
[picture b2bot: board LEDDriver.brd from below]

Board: 2 copper layers, 43.1 x 48.2 mm, 28 parts (3 on the bottom side), 18 nets.

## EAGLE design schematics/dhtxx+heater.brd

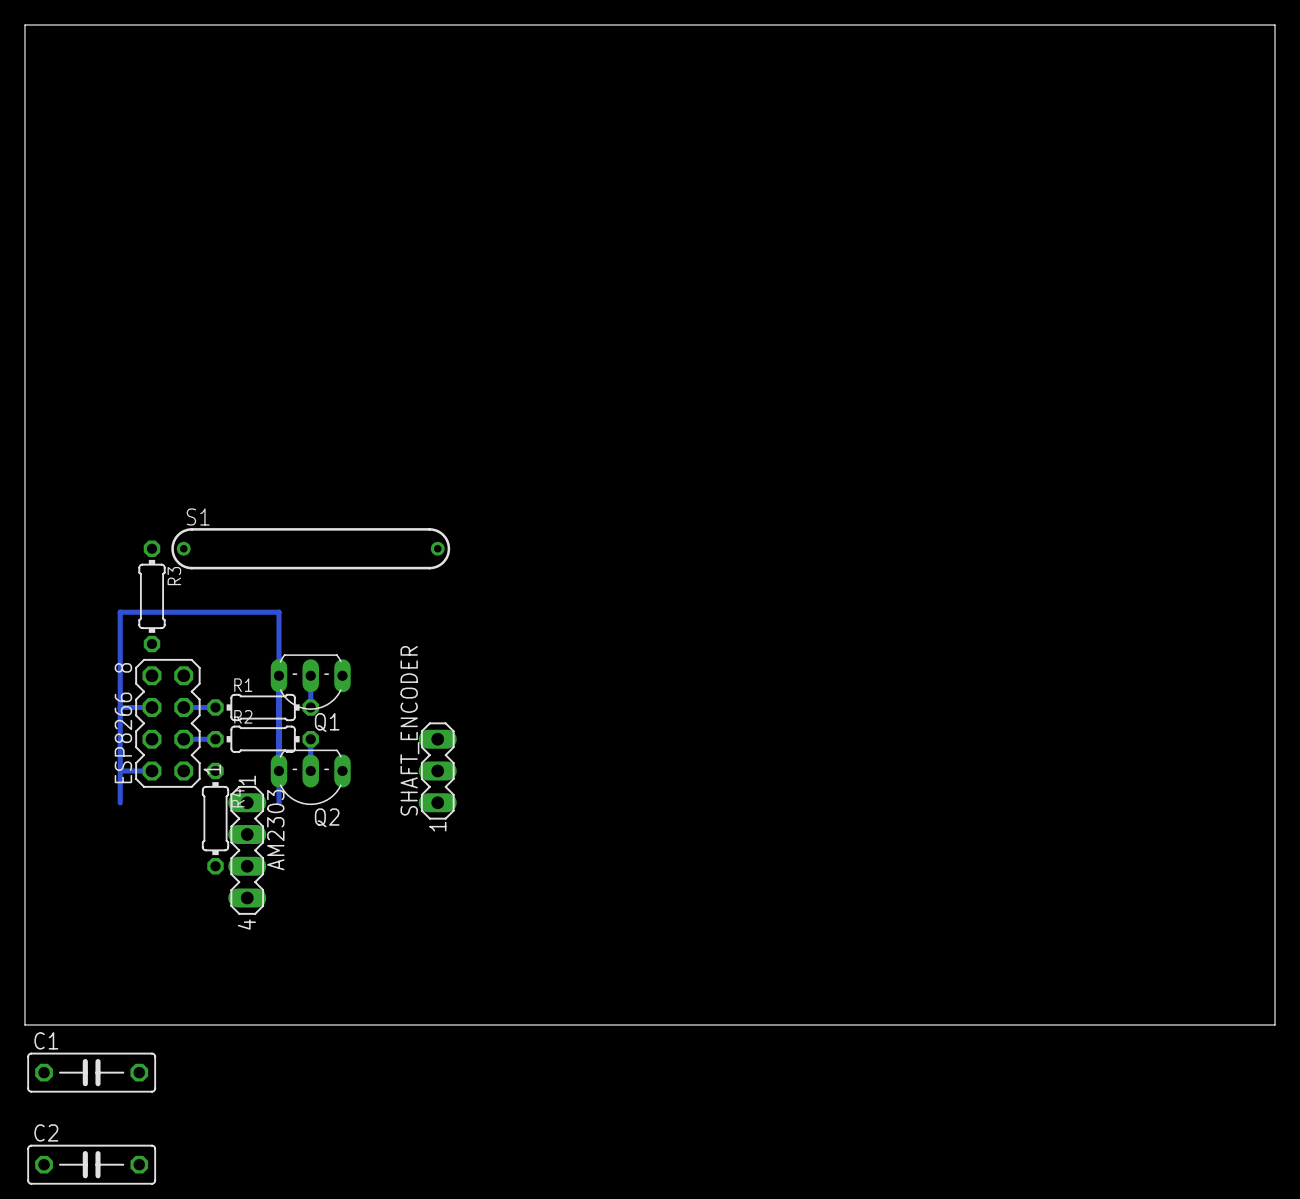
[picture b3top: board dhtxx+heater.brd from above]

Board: 2 copper layers, 100.0 x 80.0 mm, 12 parts (0 on the bottom side), 12 nets.

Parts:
AM2303: MA04-1
C1, C2: 10n; C075-032X103
ESP8266: MA04-2
Q1, Q2: BC557; TO92-EBC
R1, R2, R3, R4: 2k2; 0204/7
S1: WINDOW; MK6-8-A
SHAFT_ENCODER: Sparmatic Basic; MA03-1

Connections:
+3V3: AM2303.1, C1.1, C2.1, ESP8266.2, ESP8266.6, Q1.E, Q2.E, SHAFT_ENCODER.1
GND: AM2303.4, ESP8266.7, S1.2
GPIO0: ESP8266.3, R2.1
GPIO1(TXD): ESP8266.8, R3.2
GPIO2: ESP8266.5, R1.1
GPIO3(RXD): ESP8266.1, R4.1
unnamed: Q1.B, R1.2
unnamed: Q2.B, R2.2
unnamed: R3.1, S1.1
unnamed: C2.2, Q2.C, SHAFT_ENCODER.2
unnamed: C1.2, Q1.C, SHAFT_ENCODER.3
unnamed: AM2303.2, R4.2

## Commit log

2015-02-12 Add inital Art-Net node
2015-03-29 Add schematic with step up converter for each color
2015-03-31 Use pwm as art net output
2015-03-31 Use pwm driver from sdk v1.0.0
2015-03-31 Clean not needed functions
2015-03-31 Update pwm value only on art net changes
2015-03-31 Use Xl6009 instead of tl494 -> less power loss
2015-03-31 Do not comite qt user file
2015-03-31 Add art net node version v1.3
2015-03-31 Add new make file (faster uploading)
2015-03-31 Remove bianry files
2015-03-31 Add correct make file
2015-03-31 Add Q Light controll project for testing the art net node
2015-03-31 Ignore web page binary
2015-03-31 Disable stdout for increasing performance
2015-03-31 Automatically disable ap mode, if successfully connected to station
2015-03-31 Make uart for dmx output configurable -> use uart 0, because of pinout of ESP-01
2015-04-01 Add configuartion web interface for the art net addresses
2015-04-01 Save art net addresse persistant in flash
2015-04-01 Save art net config in flash
2015-04-01 Fix arry pointer overflow
2015-04-01 Fix art net addressing ranges
2015-04-01 Ignore DMX definitions if dmx output not activatet
2015-04-01 fix buffer overflow read. only copy length of package dmx data
2015-04-01 Do not update pwm outputs, if the art net package does not contain data for the pwm outputs
2015-04-01 Make cpu clock configurable
2015-04-02 Disable system logging, if ebugging is disabled
2015-04-02 Remove os_printf pre diff because it will be overwritten
2015-04-02 Add fixed qlc project
2015-04-02 Stop dhcp server if ap mode disabled
2015-04-22 Use Xl6009 with op amp as current source for leds
2015-04-28 Switch LEDs off after start up
2015-06-12 Add test results for energy consumption
2015-06-17 Add copyright to files
2015-07-29 Deepsleep tested
2015-07-29 Timing test reuslts
2015-07-29 Remove not needed files from fork
2015-07-29 Move mqtt lib to source directory
2015-07-29 Remove not needed hidden files
2015-07-29 Add mqtt to make file
2015-07-29 Add configuration
2015-07-29 Fix type conflicts with type casts
2015-10-20 Add version v1.5
2015-10-20 Fix includes for sdk version 1.4
2015-10-20 Set correct enviorment pathes in make file
2015-10-20 Move to Source direcotry
2015-10-20 Remove not needed files
2015-10-20 Remove no longer needed files
2015-11-11 Remove not needed web files
2015-11-11 Fix mqtt compile errors
2015-11-11 Disable logging
2015-11-11 Remove not needed line breaks and decriptions
2015-11-11 remove not needed images
2015-11-11 Disable web logging
2016-01-13 Get style sheets from externel sources
2016-01-13 Describe MQTT broker
2016-01-13 Get all resource files from github repo
2016-01-14 Add configuration web page for art net
2016-01-14 Move Art-Net and PWM output to own modules
2016-01-14 Remove old ESPFS files
2016-01-14 Ignore ESP FS make executable
2016-01-14 Update Qt Creator project files
2016-01-15 Use advanced logging
2016-01-15 Add PWM output to mqtt
2016-01-15 Make PWM output topics configurable
2016-01-15 Enter deep sleep, if all PWM outputs are disabled
2016-01-15 Really disable Art-Net and PWM output if disabled in make file
2016-01-15 Implement heater shaft encoder control
2016-01-15 Set corrcet pin function
2016-01-15 Add DHT driver with MQTT publisher
2016-01-16 Make MQTT topic vor DHTxx configurable
2016-02-01 Add sechematics for heater and DHTxx sesor
2016-02-01 Add TODO task
2016-02-01 Add pull downs to enable pins of LEDs to not flash up the LEDs on boot time
2016-02-01 Switch OpAmp of, if all LEDs are off
2016-02-05 Add initial dimmer schematic
2016-02-06 Driectly drive MOSFET (No mathing MOSFET found)
2016-02-06 Add board size
2016-02-14 Use own package for SMPS
2016-02-14 Add tasters
2016-02-14 Rename wall dimmer
2016-02-14 Add layout for dimmer for socket
2016-02-17 Add SMPS with correct dimmensions
2016-02-21 Add L dimension
2016-02-24 Make board less higher
2016-03-02 detect not working firmware (execptions or timeout for wifi connection)
2016-03-02 Use 2nd stage bootloader config section to store upgrade successful state
2016-03-02 Check for exceptions in pre init phase
2016-03-02 Move safe upgrade to own files
2016-03-02 Undo not needed changes
2016-03-02 Calulate bootloader config addresse from ET_BLANK
2016-03-02 Use better schematic
2016-03-02 Add todo tasks for schematics
2016-03-02 Reduce changes to esp-link
2016-03-02 Add readme info from WLAN RGB para
2016-03-03 Fix merge mistakes
2016-03-03 Only use mqtt_cmd if mqtt and cmd is enabled
2016-03-03 Disable all logging
2016-03-03 Exclude status if advanced CGI is not used
2016-03-03 Exclude artnet CGI is artnet is disabled
2016-03-03 Dsiabel all remeining printf messages
2016-03-06 Connect correct pins for boot mode
2016-03-16 Add more detailed flash mapping description
2016-03-18 Describe SDK flash usage
2016-03-18 use 0x40000 for user2.bin instead of 0x41000 with a 512KB SPI flash
2016-03-18 Increase ROM size
2016-03-19 Move esp-link parameters to the end of the SPI flash (More size for the partitions)
2016-03-20 Fix wiflash options bug
2016-03-21 Fit into first partition with external wifi bootloader
2016-03-23 Rename user binaries with SPI flash dest address
2016-03-23 Fix wiflash recursive call
2016-03-23 Calculate correct user config parameters address in make file
2016-03-23 Do not flashing external wifi bootloader, if already existing.
2016-03-24 Reduce redundant code
2016-03-24 Move all IO modules to the IO directory
2016-03-24 DO not build any mqtt parts, if mqtt is disabled
2016-03-24 Update project files
2016-03-24 Add include path for SDK
2016-03-24 Add wiflash support for flashing only the ESP FS
2016-03-24 Fix JSON response for MQTT settings
2016-03-24 Do not start flashing, if an reboot request is enquiered
2016-03-26 Invert PWM output for phase shift dimmer (for capacitive usage)
2016-03-26 Add make variables to build different targets from command line without changing source code
2016-03-26 Make user config static for all WLAN-IO variants
2016-03-26 Add PWM wiring for ESP03 phase shift dimmer
2016-03-27 Add definition for all used components
2016-03-27 Add inital zero crossing dectetion files
2016-03-27 Add interrupt handling for ZCD
2016-09-09 Sync PWM clock if fully high or low
2016-09-09 Change loggign of artnet modules
2016-09-09 Impirve readme headlines
2016-09-18 Disable safe upgrade if release build is enabled
